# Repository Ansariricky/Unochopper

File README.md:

<<<<<<< HEAD
# Hardware

This repository contains hardware design files for various products and subsystems, including but not limited to:

- Flight Controllers (FC)
- Electronic Speed Controllers (ESC)
- Radio Control Systems (RC)
- Video Transmitters (VTX)
- Power Distribution Units (PDU)
- Sensor Boards
- Companion Computers
- Other supporting avionics and embedded hardware

## Naming Convention

Project directories shall follow the format:

    <MCU_OR_CPU>_<HARDWARE>_RevX

Examples:

    STM32F405_FlightController_Rev1
    STM32F405_ESC_Rev1
    ESP32S3_RC_Rev1
    ESP32S3_VTX_Rev1
    RPiCM4_CompanionComputer_Rev1

### Rules

- Use underscores (_) as separators.
- Do not use spaces in directory names.
- MCU/CPU name must appear first.
- Hardware name must appear second.
- Revision number must appear last.

## Repository Contents

Each project directory may contain:

- Schematics
- PCB Layouts
- Manufacturing Files
- Bill of Materials (BOM)
- Assembly Documentation
- Design Notes

## Revision Policy

New hardware revisions shall be created as separate directories following the established naming convention. Previous revisions should be retained for traceability and historical reference.

=======
# Hardware

This repository contains hardware design files for various products and subsystems, including but not limited to:

- Flight Controllers (FC)
- Electronic Speed Controllers (ESC)
- Radio Control Systems (RC)
- Video Transmitters (VTX)
- Power Distribution Units (PDU)
- Sensor Boards
- Companion Computers
- Other supporting avionics and embedded hardware

## Naming Convention

Project directories shall follow the format:

    <MCU_OR_CPU>_<HARDWARE>_RevX

Examples:

    STM32F405_FlightController_Rev1
    STM32F405_ESC_Rev1
    ESP32S3_RC_Rev1
    ESP32S3_VTX_Rev1
    RPiCM4_CompanionComputer_Rev1

### Rules

- Use underscores (_) as separators.
- Do not use spaces in directory names.
- MCU/CPU name must appear first.
- Hardware name must appear second.
- Revision number must appear last.

## Repository Contents

Each project directory may contain:

- Schematics
- PCB Layouts
- Manufacturing Files
- Bill of Materials (BOM)
- Assembly Documentation
- Design Notes

## Revision Policy

New hardware revisions shall be created as separate directories following the established naming convention. Previous revisions should be retained for traceability and historical reference.

>>>>>>> 076c8ab1df7aa20a5a2c2d71f1c9e05963331e4d

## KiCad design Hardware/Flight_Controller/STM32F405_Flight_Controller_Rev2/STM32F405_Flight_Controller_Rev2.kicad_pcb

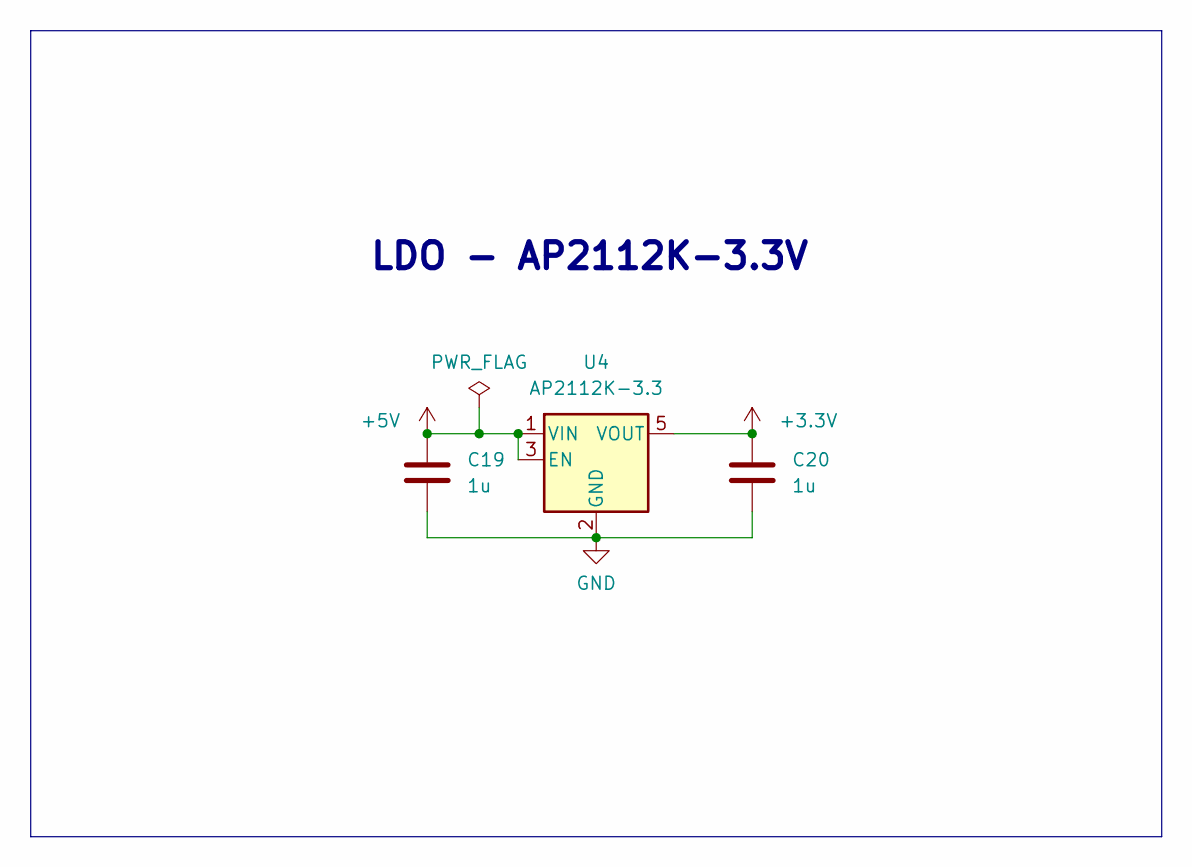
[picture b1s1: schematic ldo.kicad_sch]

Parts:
C19, C20: 1u; C_0603_1608Metric_Pad1.08x0.95mm_HandSolder
U4: AP2112K-3.3; SOT-23-5

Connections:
+3.3V: C20.1, U4.5 (VOUT); also elsewhere on the board
+5V: C19.1, U4.1 (VIN), U4.3 (EN); also elsewhere on the board
GND: C19.2, C20.2, U4.2 (GND); also elsewhere on the board

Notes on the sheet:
LDO - AP2112K-3.3V

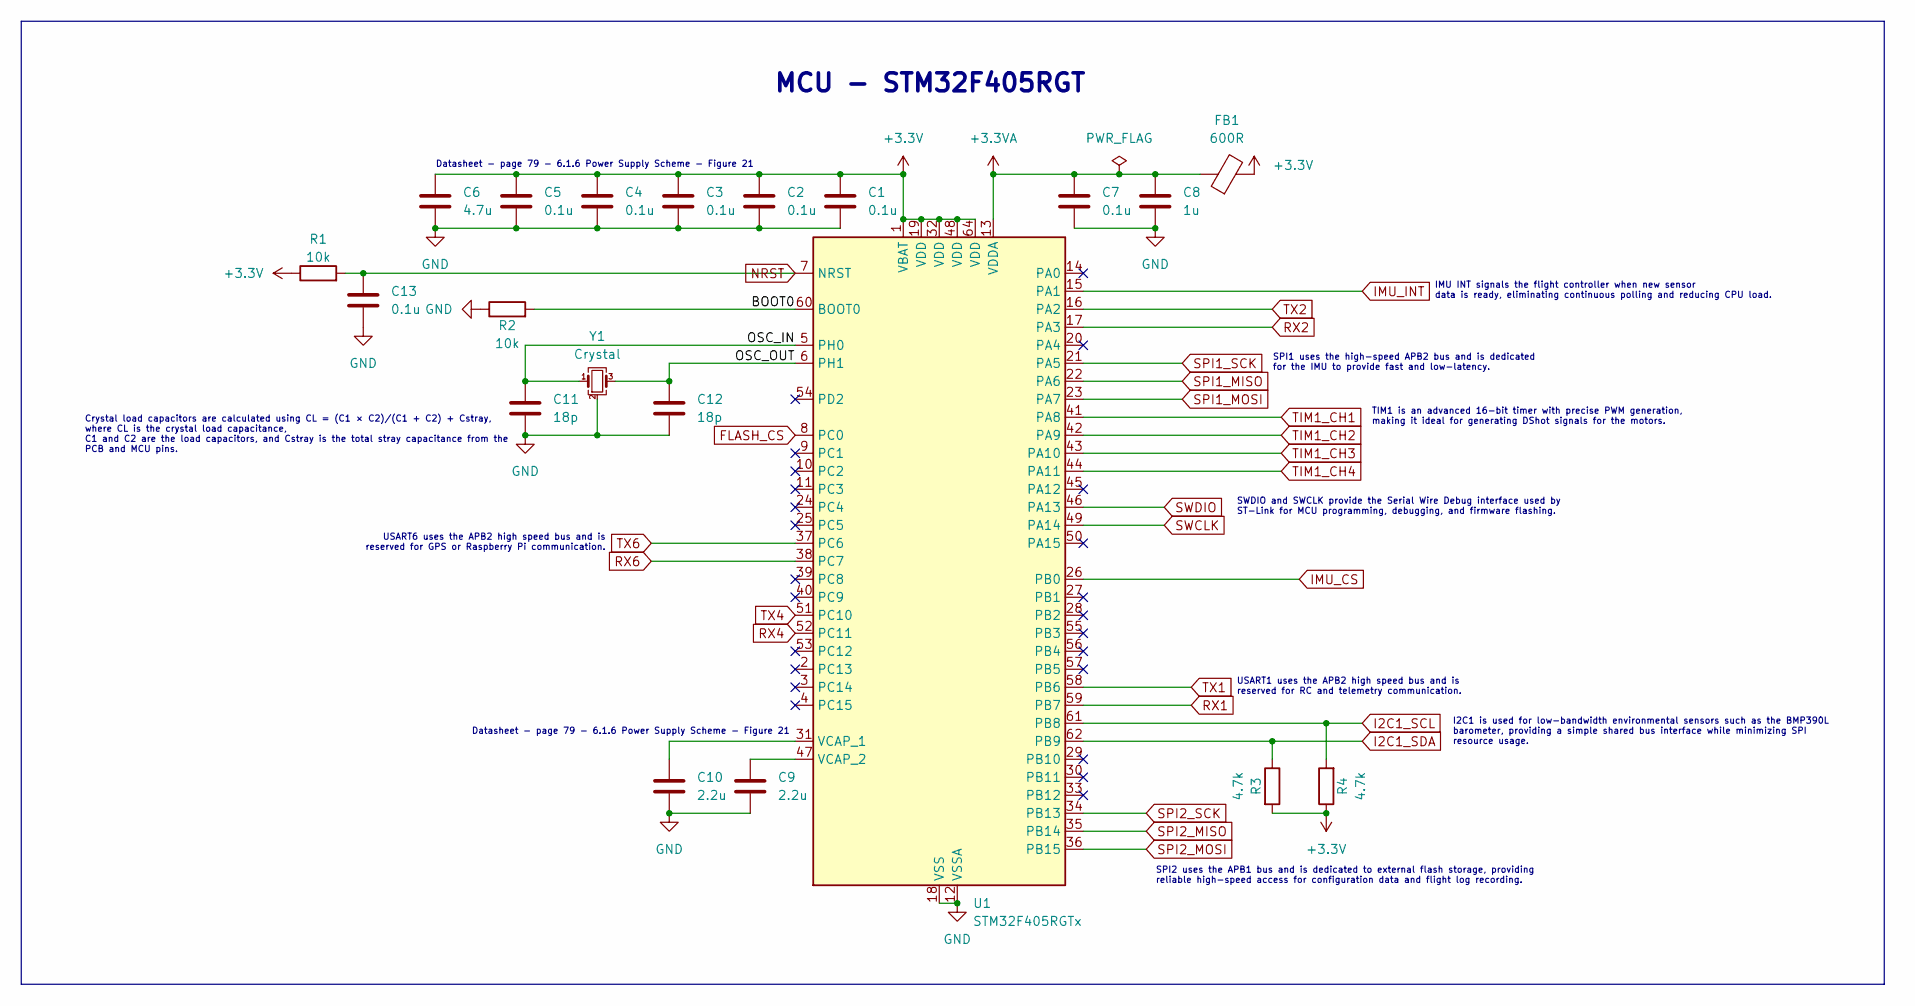
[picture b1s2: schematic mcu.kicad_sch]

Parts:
C1, C2, C3, C4, C5, C7, C13: 0.1u; C_0603_1608Metric_Pad1.08x0.95mm_HandSolder
C6: 4.7u; C_0603_1608Metric_Pad1.08x0.95mm_HandSolder
C8: 1u; C_0603_1608Metric_Pad1.08x0.95mm_HandSolder
C9, C10: 2.2u; C_0603_1608Metric_Pad1.08x0.95mm_HandSolder
C11, C12: 18p; C_0603_1608Metric_Pad1.08x0.95mm_HandSolder
FB1: 600R; L_0603_1608Metric_Pad1.05x0.95mm_HandSolder
R1, R2: 10k; R_0603_1608Metric_Pad0.98x0.95mm_HandSolder
R3, R4: 4.7k; R_0603_1608Metric_Pad0.98x0.95mm_HandSolder
U1: STM32F405RGTx; LQFP-64_10x10mm_P0.5mm
Y1: Crystal; Crystal_SMD_3225-4Pin_3.2x2.5mm_HandSoldering

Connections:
+3.3V: C1.1, C2.1, C3.1, C4.1, C5.1, C6.1, FB1.2, R1.1, R3.2, R4.1, U1.1 (VBAT), U1.19 (VDD), U1.32 (VDD), U1.48 (VDD), U1.64 (VDD); also elsewhere on the board
+3.3VA: C7.1, C8.1, FB1.1, U1.13 (VDDA)
/MCU/BOOT0: R2.2, U1.60 (BOOT0)
/MCU/OSC_IN: C11.1, U1.5 (PH0), Y1.1
/MCU/OSC_OUT: C12.1, U1.6 (PH1), Y1.3
FLASH_CS: U1.8 (PC0); also elsewhere on the board
GND: C1.2, C2.2, C3.2, C4.2, C5.2, C6.2, C7.2, C8.2, C9.2, C10.2, C11.2, C12.2, C13.2, R2.1, U1.12 (VSSA), U1.18 (VSS), U1.63 (VSS), Y1.2 (G), Y1.4 (G); also elsewhere on the board
I2C1_SCL: R4.2, U1.61 (PB8); also elsewhere on the board
I2C1_SDA: R3.1, U1.62 (PB9); also elsewhere on the board
IMU_CS: U1.26 (PB0); also elsewhere on the board
IMU_INT: U1.15 (PA1); also elsewhere on the board
NRST: C13.1, R1.2, U1.7 (NRST)
unnamed: C10.1, U1.31 (VCAP_1)
unnamed: C9.1, U1.47 (VCAP_2)
RX1: U1.59 (PB7); also elsewhere on the board
RX2: U1.17 (PA3); also elsewhere on the board
RX4: U1.52 (PC11); also elsewhere on the board
RX6: U1.38 (PC7); also elsewhere on the board
SPI1_MISO: U1.22 (PA6); also elsewhere on the board
SPI1_MOSI: U1.23 (PA7); also elsewhere on the board
SPI1_SCK: U1.21 (PA5); also elsewhere on the board
SPI2_MISO: U1.35 (PB14); also elsewhere on the board
SPI2_MOSI: U1.36 (PB15); also elsewhere on the board
SPI2_SCK: U1.34 (PB13); also elsewhere on the board
SWCLK: U1.49 (PA14); also elsewhere on the board
SWDIO: U1.46 (PA13); also elsewhere on the board
TIM1_CH1: U1.41 (PA8); also elsewhere on the board
TIM1_CH2: U1.42 (PA9); also elsewhere on the board
TIM1_CH3: U1.43 (PA10); also elsewhere on the board
TIM1_CH4: U1.44 (PA11); also elsewhere on the board
TX1: U1.58 (PB6); also elsewhere on the board
TX2: U1.16 (PA2); also elsewhere on the board
TX4: U1.51 (PC10); also elsewhere on the board
TX6: U1.37 (PC6); also elsewhere on the board

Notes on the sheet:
MCU - STM32F405RGT
IMU INT signals the flight controller when new sensor data is ready, eliminating continuous polling and reducing CPU load.
SPI2 uses the APB1 bus and is dedicated to external flash storage, providing reliable high-speed access for configuration data and flight log recording.
Crystal load capacitors are calculated using CL = (C1 × C2)/(C1 + C2) + Cstray, where CL is the crystal load capacitance, C1 and C2 are the load capacitors, and Cstray is the total stray capacitance from the PCB and MCU pins.
USART1 uses the APB2 high speed bus and is reserved for RC and telemetry communication.
SWDIO and SWCLK provide the Serial Wire Debug interface used by ST-Link for MCU programming, debugging, and firmware flashing.
I2C1 is used for low-bandwidth environmental sensors such as the BMP390L barometer, providing a simple shared bus interface while minimizing SPI resource usage.
TIM1 is an advanced 16-bit timer with precise PWM generation, making it ideal for generating DShot signals for the motors.
SPI1 uses the high-speed APB2 bus and is dedicated for the IMU to provide fast and low-latency.
USART6 uses the APB2 high speed bus and is reserved for GPS or Raspberry Pi communication.
Datasheet - page 79 - 6.1.6 Power Supply Scheme - Figure 21

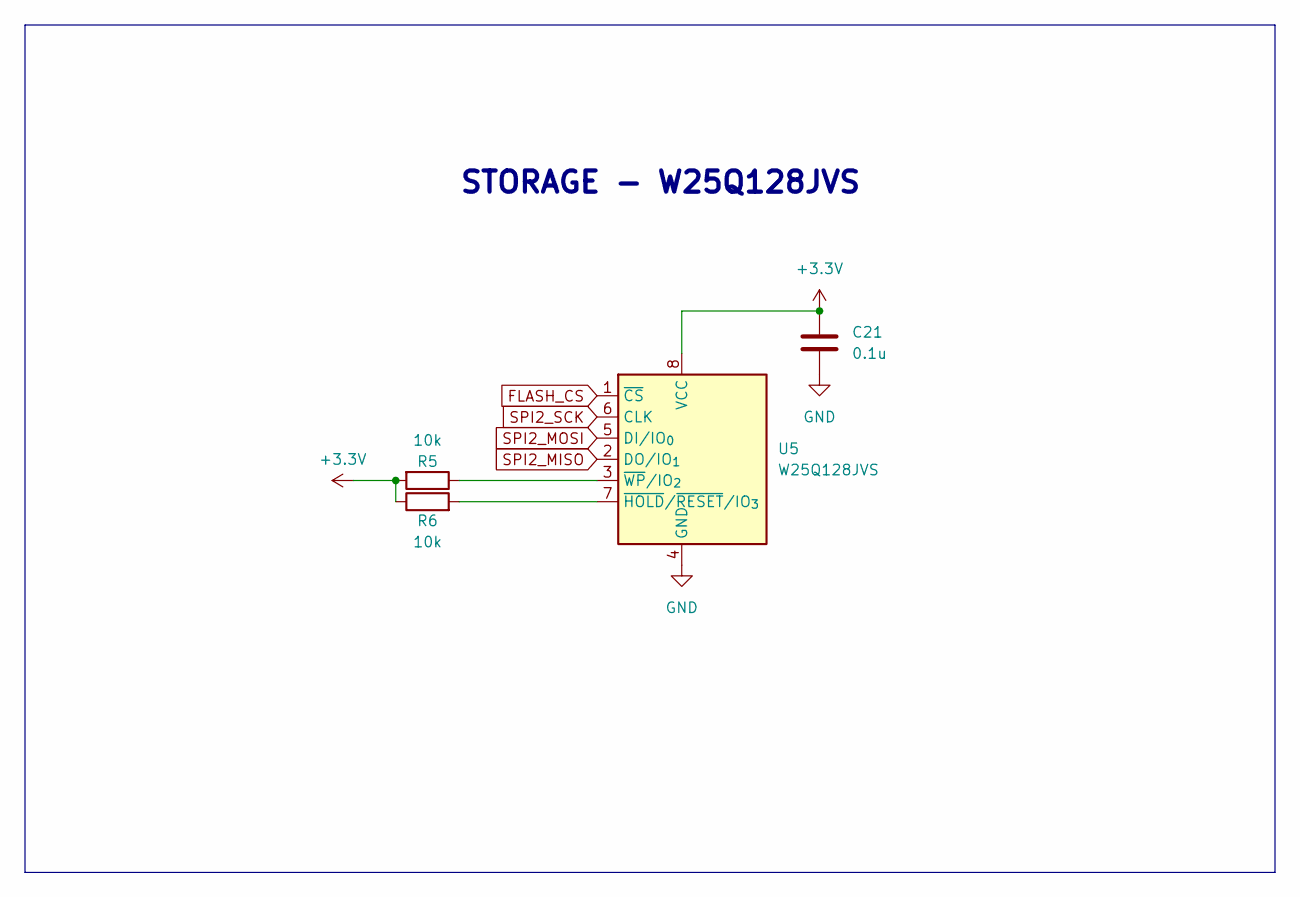
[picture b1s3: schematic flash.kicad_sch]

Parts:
C21: 0.1u; C_0603_1608Metric_Pad1.08x0.95mm_HandSolder
R5, R6: 10k; R_0603_1608Metric_Pad0.98x0.95mm_HandSolder
U5: W25Q128JVS; SOIC-8_5.3x5.3mm_P1.27mm

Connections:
+3.3V: C21.1, R5.2, R6.1, U5.8 (VCC); also elsewhere on the board
FLASH_CS: U5.1 (~CS); also elsewhere on the board
GND: C21.2, U5.4 (GND); also elsewhere on the board
unnamed: R6.2, U5.7 (~HOLD/~RESET/IO_{3})
unnamed: R5.1, U5.3 (~WP/IO_{2})
SPI2_MISO: U5.2 (DO/IO_{1}); also elsewhere on the board
SPI2_MOSI: U5.5 (DI/IO_{0}); also elsewhere on the board
SPI2_SCK: U5.6 (CLK); also elsewhere on the board

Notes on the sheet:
STORAGE - W25Q128JVS

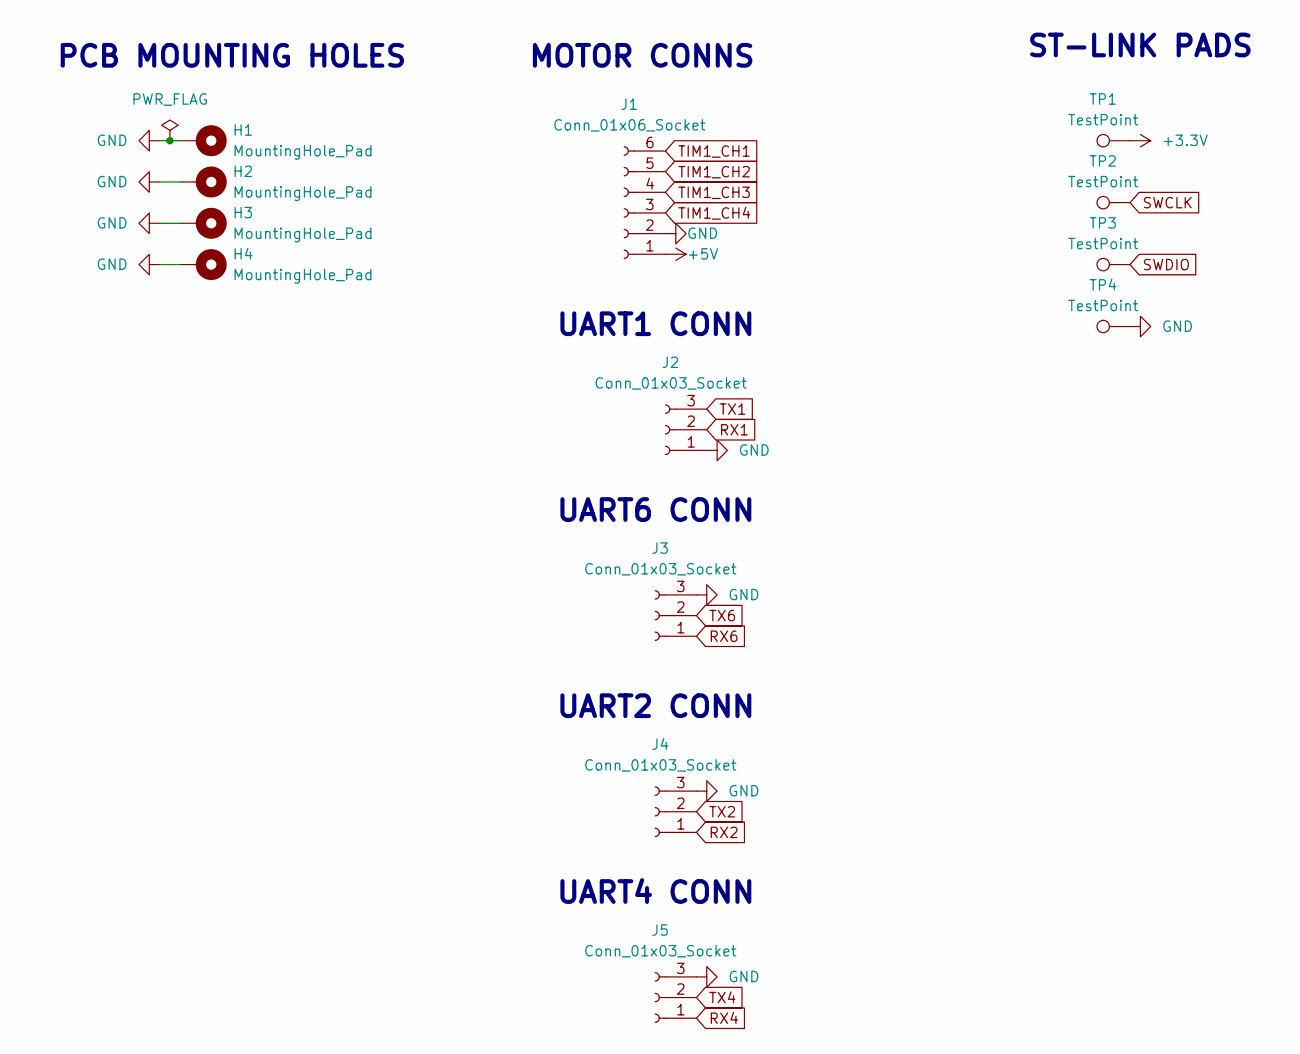
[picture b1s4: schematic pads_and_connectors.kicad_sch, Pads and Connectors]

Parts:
H1, H2, H3, H4: MountingHole_Pad; MountingHole_3.2mm_M3_Pad
J1: Conn_01x06_Socket; JST_SH_SM06B-SRSS-TB_1x06-1MP_P1.00mm_Horizontal
J2, J3, J4, J5: Conn_01x03_Socket; JST_SH_SM03B-SRSS-TB_1x03-1MP_P1.00mm_Horizontal
TP1, TP2, TP3, TP4: TestPoint; TestPoint_Pad_D1.5mm

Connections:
+3.3V: TP1.1 (1_1); also elsewhere on the board
+5V: J1.1; also elsewhere on the board
GND: H1.1 (1_1), H2.1 (1_1), H3.1 (1_1), H4.1 (1_1), J1.2, J2.1, J3.3, J4.3, J5.3, TP4.1 (1_1); also elsewhere on the board
RX1: J2.2; also elsewhere on the board
RX2: J4.1; also elsewhere on the board
RX4: J5.1; also elsewhere on the board
RX6: J3.1; also elsewhere on the board
SWCLK: TP2.1 (1_1); also elsewhere on the board
SWDIO: TP3.1 (1_1); also elsewhere on the board
TIM1_CH1: J1.6; also elsewhere on the board
TIM1_CH2: J1.5; also elsewhere on the board
TIM1_CH3: J1.4; also elsewhere on the board
TIM1_CH4: J1.3; also elsewhere on the board
TX1: J2.3; also elsewhere on the board
TX2: J4.2; also elsewhere on the board
TX4: J5.2; also elsewhere on the board
TX6: J3.2; also elsewhere on the board

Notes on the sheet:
UART2 CONN
UART4 CONN
UART1 CONN
MOTOR CONNS
UART6 CONN
PCB MOUNTING HOLES
ST-LINK PADS

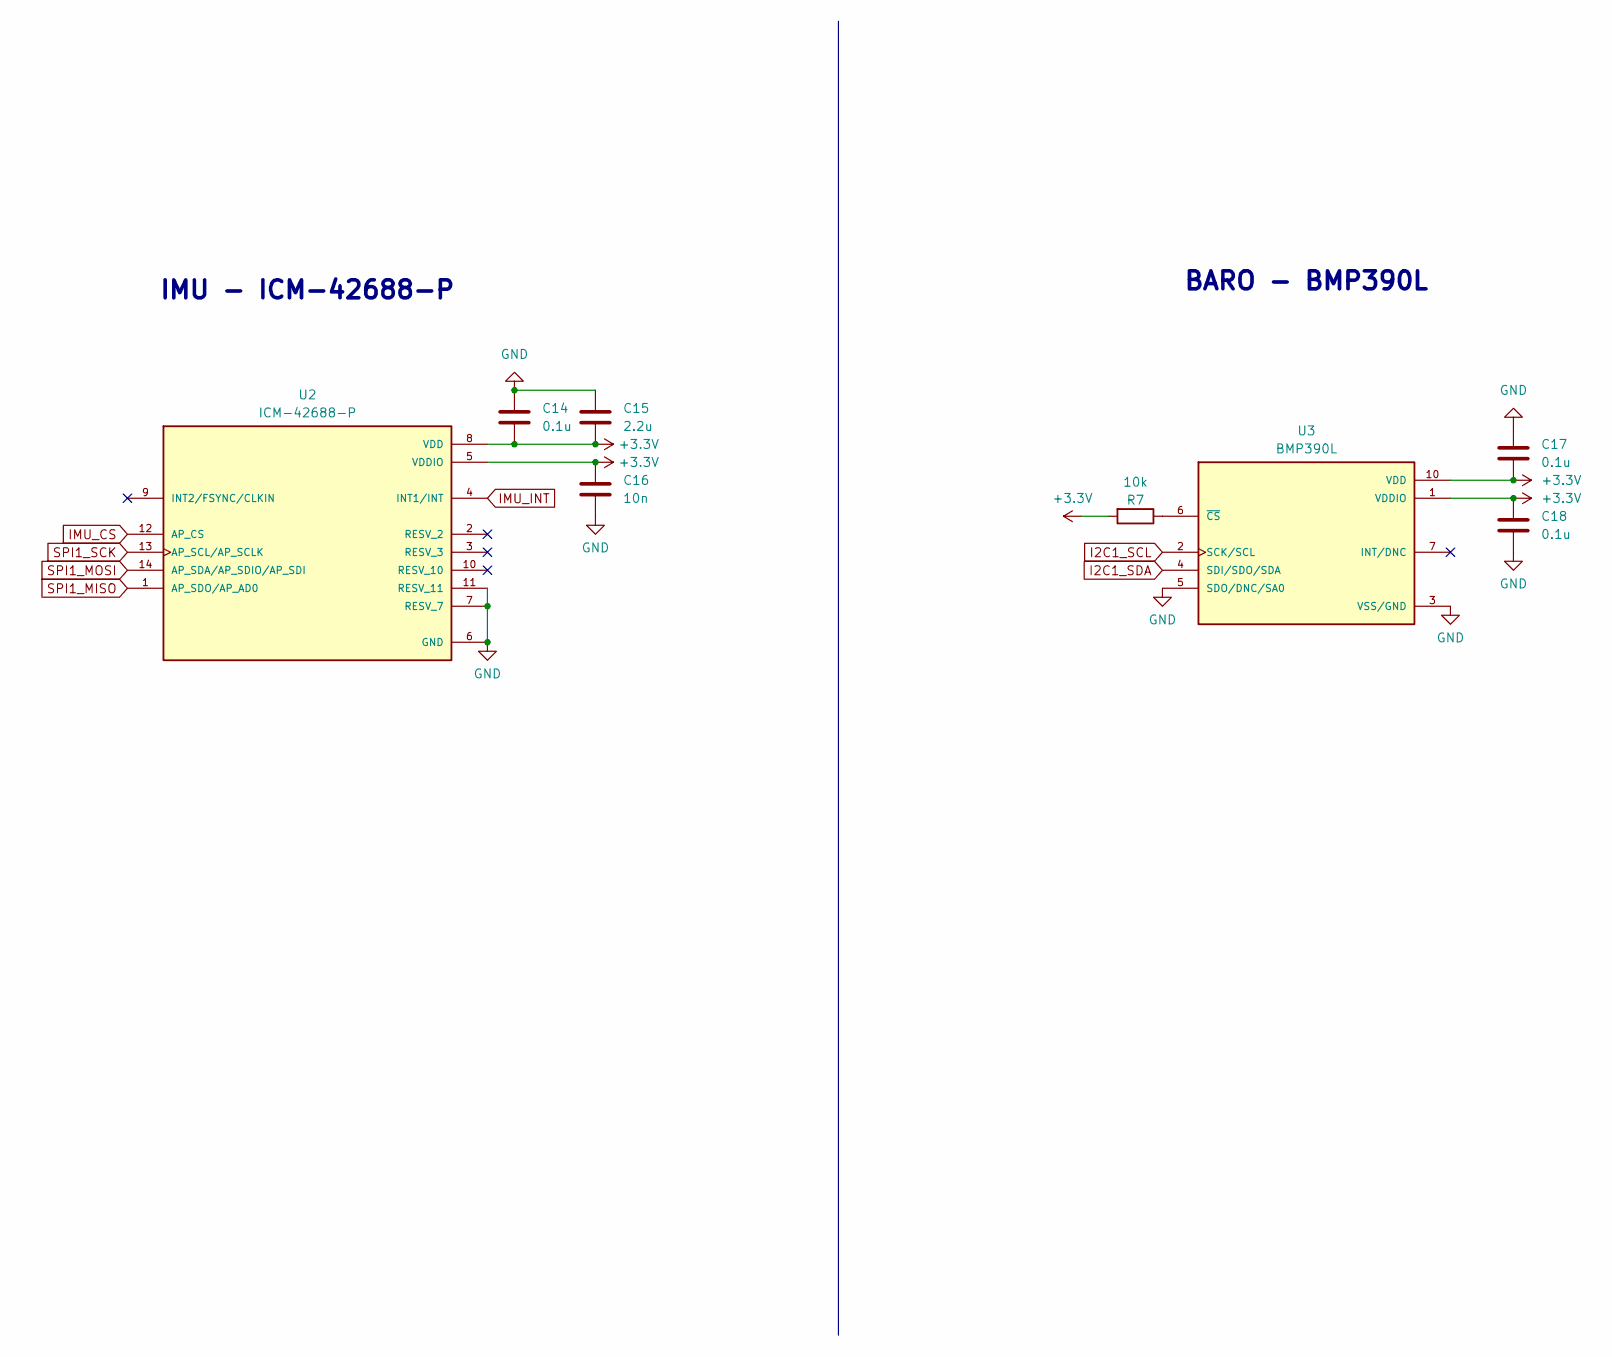
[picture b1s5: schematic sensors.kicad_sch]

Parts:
C14, C17, C18: 0.1u; C_0603_1608Metric_Pad1.08x0.95mm_HandSolder
C15: 2.2u; C_0603_1608Metric_Pad1.08x0.95mm_HandSolder
C16: 10n; C_0603_1608Metric_Pad1.08x0.95mm_HandSolder
R7: 10k; R_0603_1608Metric_Pad0.98x0.95mm_HandSolder
U2: ICM-42688-P; PARTREV 1.2
U3: BMP390L; PARTREV 1.7

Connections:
+3.3V: C14.2, C15.2, C16.1, C17.1, C18.1, R7.2, U2.5 (VDDIO), U2.8 (VDD), U3.1 (VDDIO), U3.10 (VDD); also elsewhere on the board
GND: C14.1, C15.1, C16.2, C17.2, C18.2, U2.6 (GND), U2.7 (RESV_7), U2.11 (RESV_11), U3.3 (VSS/GND), U3.5 (SDO/DNC/SA0), U3.8 (VSS/GND), U3.9 (VSS/GND); also elsewhere on the board
I2C1_SCL: U3.2 (SCK/SCL); also elsewhere on the board
I2C1_SDA: U3.4 (SDI/SDO/SDA); also elsewhere on the board
IMU_CS: U2.12 (AP_CS); also elsewhere on the board
IMU_INT: U2.4 (INT1/INT); also elsewhere on the board
unnamed: R7.1, U3.6 (~CS)
SPI1_MISO: U2.1 (AP_SDO/AP_AD0); also elsewhere on the board
SPI1_MOSI: U2.14 (AP_SDA/AP_SDIO/AP_SDI); also elsewhere on the board
SPI1_SCK: U2.13 (AP_SCL/AP_SCLK); also elsewhere on the board

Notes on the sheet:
IMU - ICM-42688-P
BARO - BMP390L

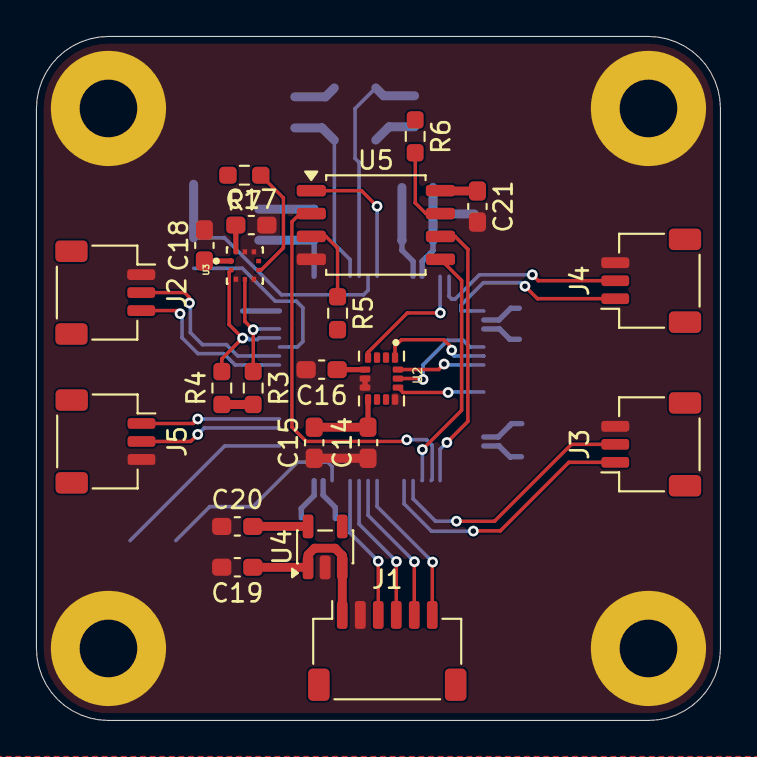
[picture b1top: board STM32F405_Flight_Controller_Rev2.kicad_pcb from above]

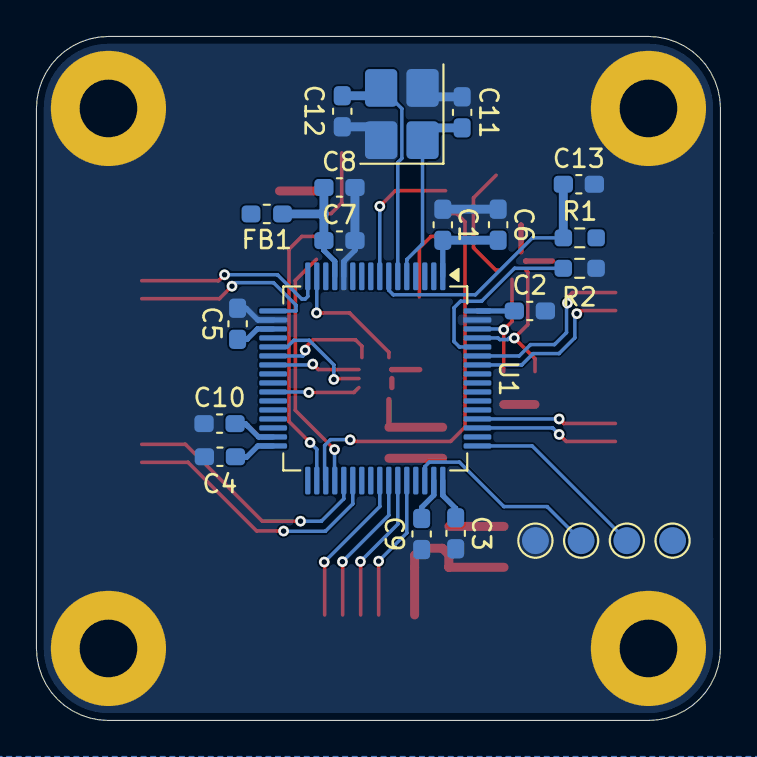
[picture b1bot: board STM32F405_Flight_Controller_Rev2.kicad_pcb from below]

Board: 4 copper layers, 38.0 x 38.0 mm, 48 parts (22 on the bottom side), 38 nets.

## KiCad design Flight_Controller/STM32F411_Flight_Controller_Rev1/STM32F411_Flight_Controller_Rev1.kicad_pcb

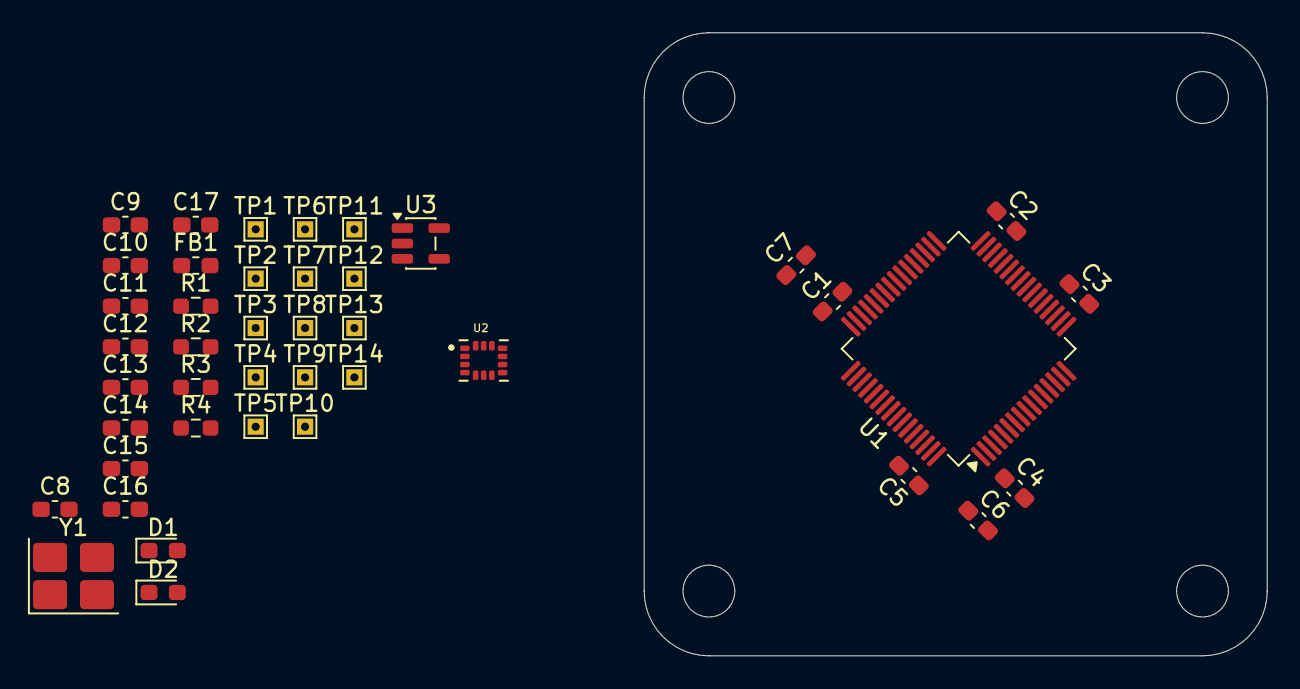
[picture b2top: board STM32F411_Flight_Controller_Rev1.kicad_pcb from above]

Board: 4 copper layers, 38.5 x 38.5 mm, 46 parts (0 on the bottom side), 27 nets, no tracks yet.

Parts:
C1, C2, C3, C4, C5, C6, C8, C13: 0.1u; C_0603_1608Metric_Pad1.08x0.95mm_HandSolder
C7, C10: 4.7u; C_0603_1608Metric_Pad1.08x0.95mm_HandSolder
C9, C16, C17: 1u; C_0603_1608Metric_Pad1.08x0.95mm_HandSolder
C11, C12: 18p; C_0603_1608Metric_Pad1.08x0.95mm_HandSolder
C14: 2.2u; C_0603_1608Metric_Pad1.08x0.95mm_HandSolder
C15: 10n; C_0603_1608Metric_Pad1.08x0.95mm_HandSolder
D1: RED; LED_0603_1608Metric_Pad1.05x0.95mm_HandSolder
D2: GREEN; LED_0603_1608Metric_Pad1.05x0.95mm_HandSolder
FB1: 600R; L_0603_1608Metric_Pad1.05x0.95mm_HandSolder
H1, H2, H3, H4: MountingHole; MountingHole_3.2mm_M3
R1, R2: 10k; R_0603_1608Metric_Pad0.98x0.95mm_HandSolder
R3, R4: 330; R_0603_1608Metric_Pad0.98x0.95mm_HandSolder
TP1, TP2, TP3, TP4, TP5, TP6, TP7, TP8, TP9, TP10, TP11, TP12, TP13, TP14: TestPoint; TestPoint_THTPad_1.0x1.0mm_Drill0.5mm
U1: STM32F411RETx; LQFP-64_10x10mm_P0.5mm
U2: ICM-42688-P
U3: AP2112K-3.3; SOT-23-5
Y1: Crystal; Crystal_SMD_3225-4Pin_3.2x2.5mm_HandSoldering

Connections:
+3.3V: C1.1, C2.1, C3.1, C4.1, C5.1, C6.1, C7.1, C13.1, C14.1, C17.2, D1.2 (A), D2.2 (A), FB1.1, R1.1, TP11.1 (1_1), U1.1 (VBAT), U1.19 (VDD), U1.32 (VDD), U1.48 (VDD), U1.64 (VDD), U2.8 (VDD), U3.5 (VOUT)
+3.3VA: C8.1, C9.1, C15.2, FB1.2, U1.13 (VDDA), U2.5 (VDDIO)
/BOOT0: R2.2, U1.60 (BOOT0)
/HSE_IN: C11.1, U1.5 (PH0), Y1.1
/HSE_OUT: C12.1, U1.6 (PH1), Y1.3
/IMU_CS: U1.61 (PB8), U2.12 (AP_CS)
/IMU_INT: U1.54 (PD2), U2.4 (INT1/INT)
/LDO_5V_IN: C16.2, TP13.1 (1_1), U3.1 (VIN), U3.3 (EN)
/NRST: R1.2, U1.7 (NRST)
/NSTAT_LED: R4.2, U1.16 (PA2)
/RX1: TP8.1 (1_1), U1.59 (PB7)
/RX6: TP10.1 (1_1), U1.38 (PC7)
/SPI1_MISO: U1.56 (PB4), U2.1 (AP_SDO/AP_AD0)
/SPI1_MOSI: U1.57 (PB5), U2.14 (AP_SDA/AP_SDIO/AP_SDI)
/SPI1_SCK: U1.55 (PB3), U2.13 (AP_SCL/AP_SCLK)
/SWCLK: TP6.1 (1_1), U1.49 (PA14)
/SWDIO: TP5.1 (1_1), U1.46 (PA13)
/TIM1_CH1: TP1.1 (1_1), U1.41 (PA8)
/TIM1_CH2: TP2.1 (1_1), U1.42 (PA9)
/TIM1_CH3: TP3.1 (1_1), U1.43 (PA10)
/TIM1_CH4: TP4.1 (1_1), U1.44 (PA11)
/TX1: TP7.1 (1_1), U1.58 (PB6)
/TX6: TP9.1 (1_1), U1.37 (PC6)
GND: C1.2, C2.2, C3.2, C4.2, C5.2, C6.2, C7.2, C8.2, C9.2, C10.2, C11.2, C12.2, C13.2, C14.2, C15.1, C16.1, C17.1, R2.1, R3.2, TP12.1 (1_1), TP14.1 (1_1), U1.12 (VSSA), U1.18 (VSS), U1.31 (VSS), U1.47 (VSS), U1.63 (VSS), U2.6 (GND), U2.7 (RESV_7), U2.11 (RESV_11), U3.2 (GND), Y1.2 (G), Y1.4 (G)
unnamed: D1.1 (K), R3.1
unnamed: D2.1 (K), R4.1
unnamed: C10.1, U1.30 (VCAP1)

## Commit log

2026-06-17 Add repository README
2026-06-17 Separate hardware and firmware
2026-06-17 Add firmware
2026-06-20 Ready Rev2 PCB
